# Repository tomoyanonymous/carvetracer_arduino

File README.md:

# Simple Curve Tracer Shield for Arduino Uno

A shield circuit board for Arduino Uno to analyze the characteristics of a transistor of FET with minimal components.

2023.04 Matsuura Tomoya

## Required Components

- Rail-to-Rail Op Amp(DIP8 Package) x1
- Resistors
    - 100k x 5
    - 1k x 1
    - 9k x 1
- Capacitors
    - 0.1uF(104) x 1
    - 0.2uF(204) x 1
- SPDT Switch(or, 3-Pin header w/ Jumper Pin)
- 3 Pin Deep Socket for Transistor x 2
- 2.54mm Pin Header for Arduino Socket

## Required Softwares

- Arduino IDE
- Processing
- KiCad

## How To Use the Shield

1. Connect Arduino to PC
1. Open Examples->Firmata->StandardFirmata
1. Upload it
1. Stack the shield onto Arduino
1. Check the polarity of the slide switch depending on what types of transistor you are going to test(NPN/NMOS or PNP/PMOS).
1. Open curvetrace_firmata.pde with Processing and run it.
1. Hit "s" key and it will start plotting.

## Reference 

This project is heavily based on the Project below.

**Arduino BiCMOS Curve Tracer by Don Sauer**

http://www.idea2ic.com/BiCmosCurveTracer/Arduino%2520BiCmos%2520Curve%2520Tracer.html

The hardware structure is mostly the same. 200k resistor is replaced with 100k resistor*2 for the simplicity.

The original software uses raw serial connection between Arduino and Processing. I merged the two codes into 1 Processing sketch by using [Firmata](https://docs.arduino.cc/hacking/software/FirmataLibrary), the multi-purpose serial protocol for controlling arduino.

Instead, the function of exporting raw data for plotting with external application (like Octave and Scilab) is omitted.

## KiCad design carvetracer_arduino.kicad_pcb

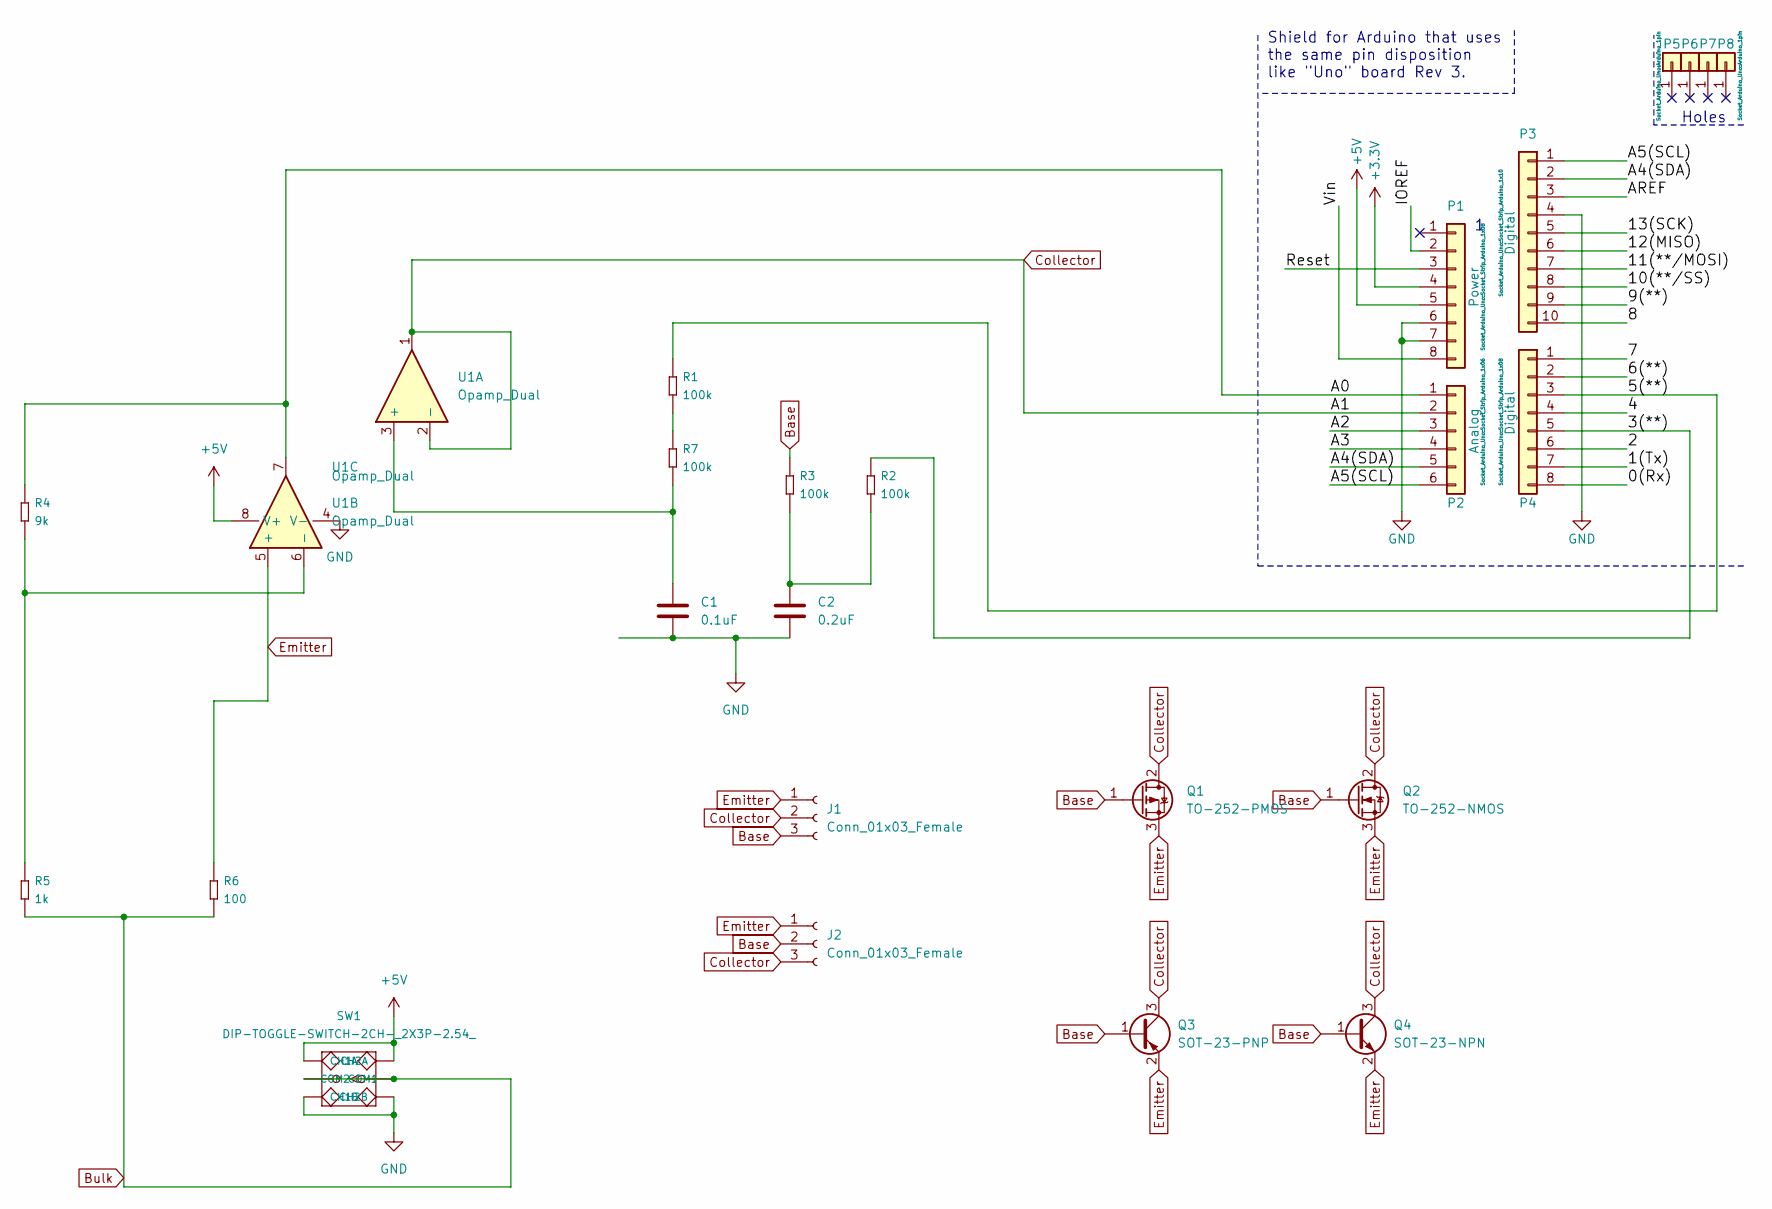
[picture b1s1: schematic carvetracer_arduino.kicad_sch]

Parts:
C1: 0.1uF; C_Rect_L9.0mm_W2.5mm_P7.50mm_MKT
C2: 0.2uF; C_Rect_L9.0mm_W2.5mm_P7.50mm_MKT
J1, J2: Conn_01x03_Female; PinHeader_1x03_P2.54mm_Vertical
P1: Power; Socket_Strip_Arduino_1x08
P2: Analog; Socket_Strip_Arduino_1x06
P3: Digital; Socket_Strip_Arduino_1x10
P4: Digital; Socket_Strip_Arduino_1x08
P5, P6, P7, P8: CONN_01X01; Arduino_1pin
Q1: TO-252-PMOS; TO-252-2
Q2: TO-252-NMOS; TO-252-2
Q3: SOT-23-PNP; SOT-23
Q4: SOT-23-NPN; SOT-23
R1, R2, R3, R7: 100k; PR-D2.3XL6.5MM; MPN FHCFR-1_4W-101J
R4: 9k; PR-D2.3XL6.5MM; MPN FHCFR-1_4W-101J
R5: 1k; PR-D2.3XL6.5MM; MPN FHCFR-1_4W-101J
R6: 100; PR-D2.3XL6.5MM; MPN FHCFR-1_4W-101J
SW1: DIP-TOGGLE-SWITCH-2CH-_2X3P-2.54_; SW6-2.54-9.0X3.5X3.2+2.0MM; MPN MS-22D18 G2 ROHS
U1: Opamp_Dual; DIP-8_W7.62mm_LongPads

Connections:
+3V3: P1.4
+5V: P1.5, SW1.CH1A, SW1.CH2A, U1.8 (V+)
/0(Rx): P4.8
/1(Tx): P4.7
/2: P4.6
/3(**): P4.5, R2.2
/4: P4.4
/5(**): P4.3, R1.2
/6(**): P4.2
/7: P4.1
/8: P3.10
/9(**): P3.9
/10(**/SS): P3.8
/11(**/MOSI): P3.7
/12(MISO): P3.6
/13(SCK): P3.5
/A0: P2.1, R4.2, U1.7
/A2: P2.3
/A3: P2.4
/A4(SDA): P2.5, P3.2
/A5(SCL): P2.6, P3.1
/AREF: P3.3
/IOREF: P1.2
/Reset: P1.3
/Vin: P1.8
Base: J1.3, J2.2, Q1.1 (G), Q2.1 (G), Q3.1 (B), Q4.1 (B), R3.2
Bulk: R5.1, R6.1, SW1.COM1, SW1.COM2
Collector: J1.2, J2.3, P2.2, Q1.2 (D), Q2.2 (D), Q3.3 (C), Q4.3 (C), U1.1, U1.2 (-)
Emitter: J1.1, J2.1, Q1.3 (S), Q2.3 (S), Q3.2 (E), Q4.2 (E), R6.2, U1.5 (+)
GND: C1.2, C2.2, P1.6, P1.7, P3.4, SW1.CH1B, SW1.CH2B, U1.4 (V-)
unnamed: C1.1, R7.1, U1.3 (+)
unnamed: C2.1, R2.1, R3.1
unnamed: R1.1, R7.2
unnamed: R4.1, R5.2, U1.6 (-)

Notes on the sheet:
Holes
Shield for Arduino that uses the same pin disposition like "Uno" board Rev 3.

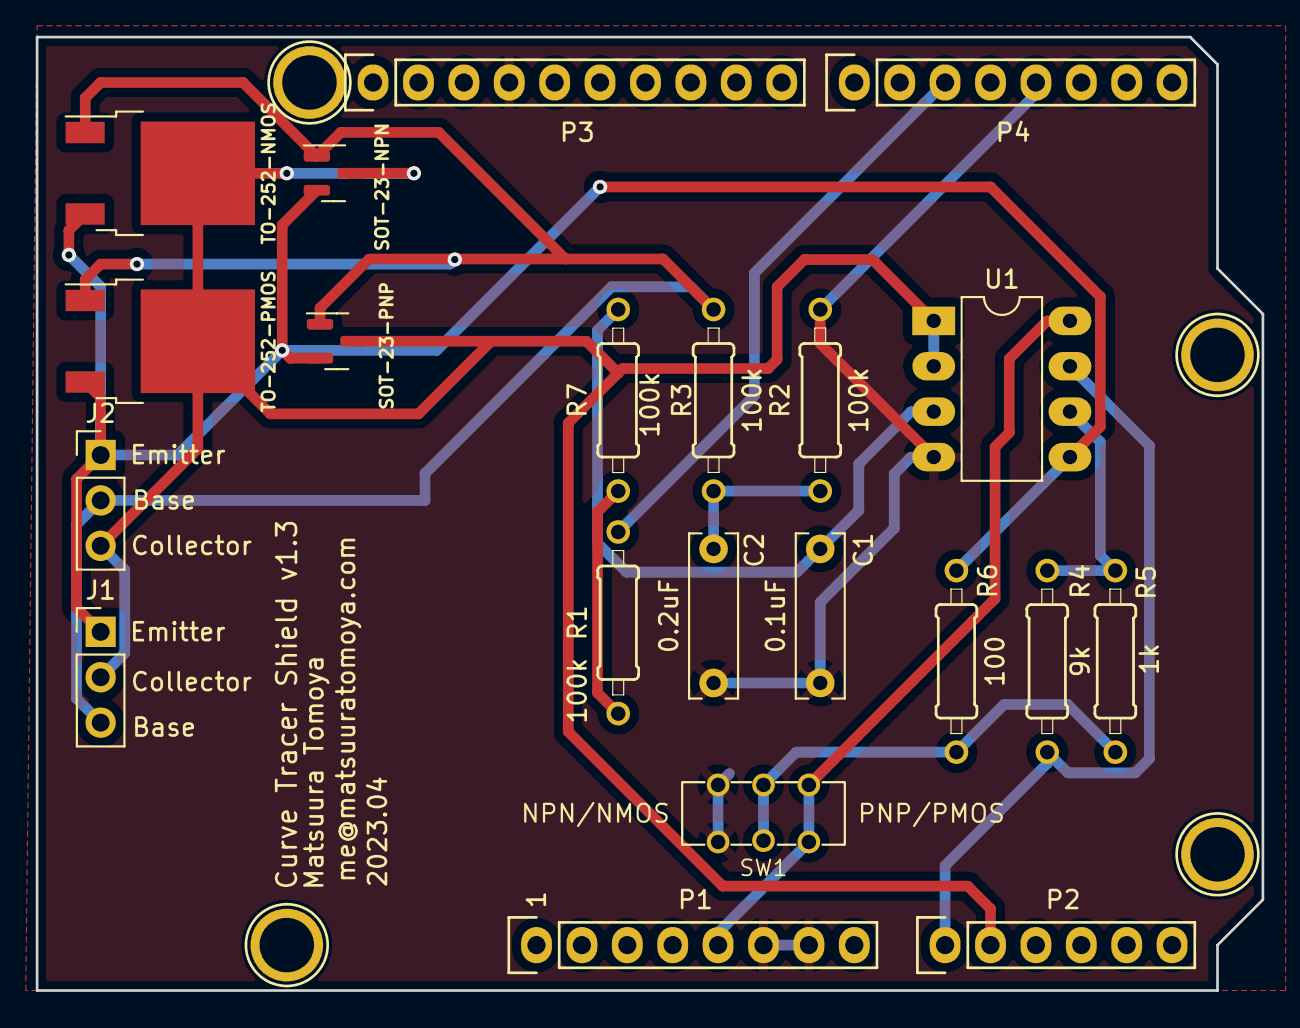
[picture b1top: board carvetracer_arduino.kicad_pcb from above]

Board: 2 copper layers, 68.6 x 53.3 mm, 25 parts (0 on the bottom side), 15 nets.

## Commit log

2023-04-22 initial commit(kicad projects)
2023-04-22 add processing code
2023-04-22 readme
